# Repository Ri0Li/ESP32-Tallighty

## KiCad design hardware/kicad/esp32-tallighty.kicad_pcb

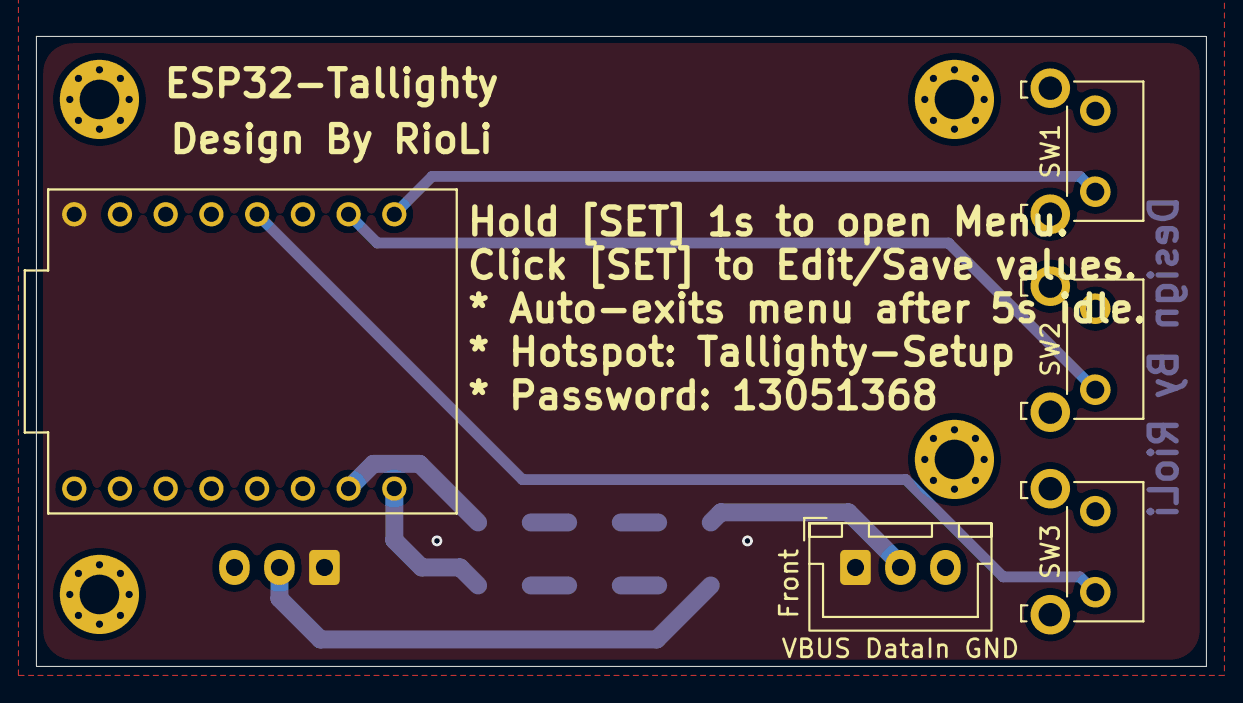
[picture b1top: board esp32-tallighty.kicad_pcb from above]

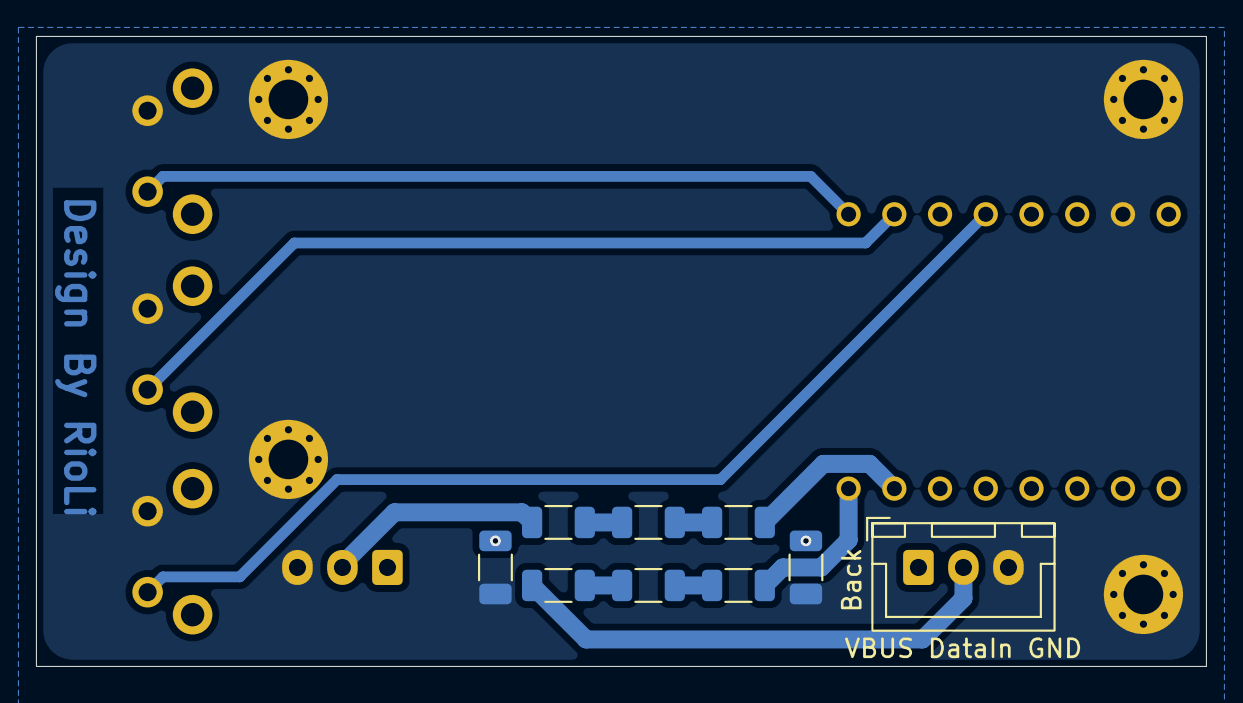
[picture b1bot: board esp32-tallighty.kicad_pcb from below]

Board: 2 copper layers, 65.0 x 35.0 mm, 18 parts (9 on the bottom side), 13 nets.

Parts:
Back: WS2812B; JST_XH_B3B-XH-A_1x03_P2.50mm_Vertical
C1, C2: 100n; C_1206_3216Metric
Front: WS2812B; JST_XH_B3B-XH-A_1x03_P2.50mm_Vertical
H1, H2, H3, H4: MountingHole_Pad; MountingHole_2.2mm_M2_Pad_Via
R1, R2, R3, R4, R5, R6: 100; R_1206_3216Metric
SW1, SW2, SW3: SW_Push; SW_Tactile_SKHH_Angled
U1: ESP32-C3_SUPERMINI_TH; MODULE_ESP32-C3_SUPERMINI_TH

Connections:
GND: Back.3 (VSS), C1.2, C2.2, Front.3 (VSS), H1.1 (1_1), H2.1 (1_1), H3.1 (1_1), H4.1 (1_1), SW1.1, SW2.1, SW3.1, U1.G (GND)
unnamed: Front.4 (DIN), R3.1
unnamed: Back.4 (DIN), R6.1
unnamed: R1.1, R2.2
unnamed: R2.1, R3.2
unnamed: R4.1, R5.2
unnamed: R5.1, R6.2
unnamed: SW1.2, U1.0 (GPIO0)
unnamed: SW2.2, U1.1 (GPIO1)
unnamed: SW3.2, U1.3 (GPIO3)
unnamed: R1.2, U1.20 (GPIO20)
unnamed: R4.2, U1.21 (GPIO21)
VBUS: Back.1 (VDD), C1.1, C2.1, Front.1 (VDD), U1.5V
